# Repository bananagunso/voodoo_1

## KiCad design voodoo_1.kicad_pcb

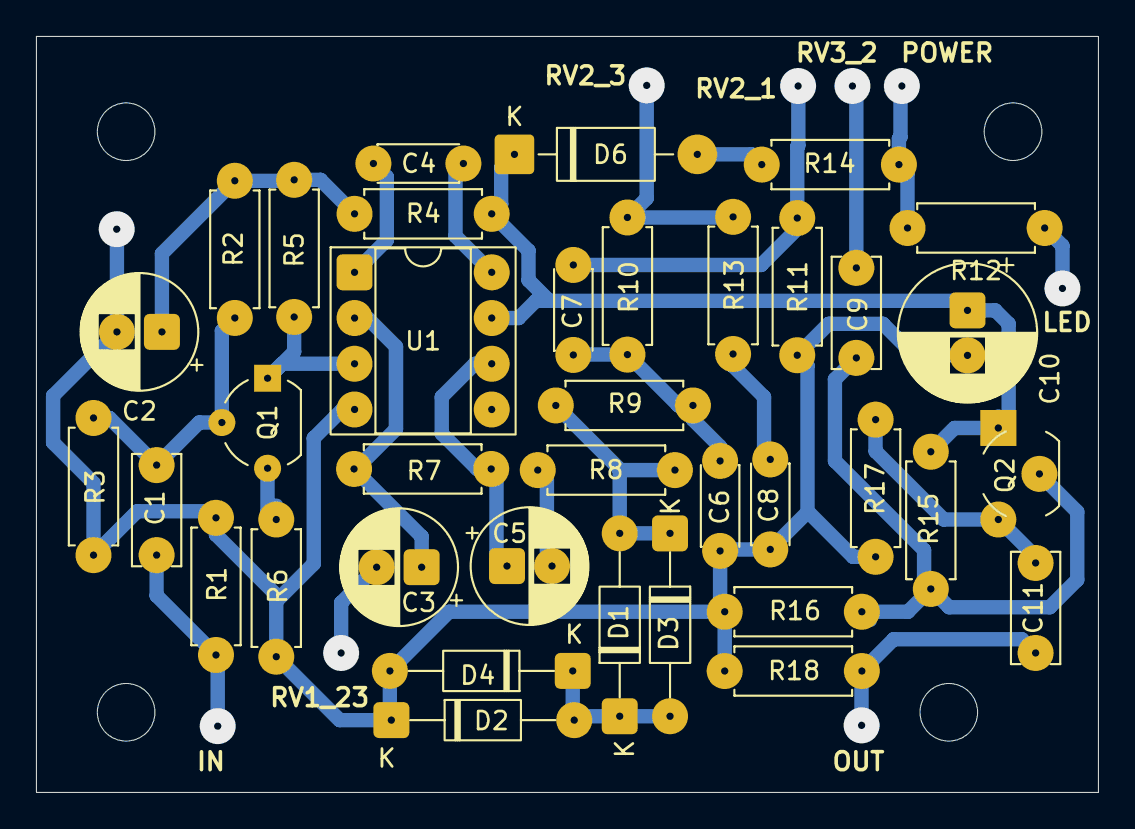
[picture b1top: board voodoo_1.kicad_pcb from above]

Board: 2 copper layers, 59.0 x 42.0 mm, 41 parts (0 on the bottom side), 23 nets.

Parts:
C1, C9, C11: 0.1u; C_Disc_D6.0mm_W2.5mm_P5.00mm
C2: 16v22u; CP_Radial_D6.3mm_P2.50mm
C3, C5: 16v2.2u; CP_Radial_D6.3mm_P2.50mm
C4: 22p; C_Disc_D4.3mm_W1.9mm_P5.00mm
C6: 3300p; C_Disc_D4.3mm_W1.9mm_P5.00mm
C7: 2200p; C_Disc_D4.3mm_W1.9mm_P5.00mm
C8: 470p; C_Disc_D4.3mm_W1.9mm_P5.00mm
C10: 16v220u; CP_Radial_D7.5mm_P2.50mm
D1, D2, D3, D4: 1N4148WT; D_DO-35_SOD27_P10.16mm_Horizontal
D6: 1N4001; D_DO-41_SOD81_P10.16mm_Horizontal
H1, H2, H3, H4: MountingHole; MountingHole_3.2mm_M3
Q1, Q2: 2N2222; TO-92_Wide
R1, R2, R18: 2.2M; R_Axial_DIN0207_L6.3mm_D2.5mm_P7.62mm_Horizontal
R3: 680k; R_Axial_DIN0207_L6.3mm_D2.5mm_P7.62mm_Horizontal
R4, R5: 47k; R_Axial_DIN0207_L6.3mm_D2.5mm_P7.62mm_Horizontal
R6: 22k; R_Axial_DIN0207_L6.3mm_D2.5mm_P7.62mm_Horizontal
R7: 150k; R_Axial_DIN0207_L6.3mm_D2.5mm_P7.62mm_Horizontal
R8, R17: 10k; R_Axial_DIN0207_L6.3mm_D2.5mm_P7.62mm_Horizontal
R9: 1.5k; R_Axial_DIN0207_L6.3mm_D2.5mm_P7.62mm_Horizontal
R10, R11: 39k; R_Axial_DIN0207_L6.3mm_D2.5mm_P7.62mm_Horizontal
R12: 5.6k; R_Axial_DIN0207_L6.3mm_D2.5mm_P7.62mm_Horizontal
R13: 12k; R_Axial_DIN0207_L6.3mm_D2.5mm_P7.62mm_Horizontal
R14: 150; R_Axial_DIN0207_L6.3mm_D2.5mm_P7.62mm_Horizontal
R15: 820k; R_Axial_DIN0207_L6.3mm_D2.5mm_P7.62mm_Horizontal
R16: 1M; R_Axial_DIN0207_L6.3mm_D2.5mm_P7.62mm_Horizontal
U1: LM308; DIP-8_W7.62mm_Socket

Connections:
+9V: R12.2, R14.1
GND: C2.2, C6.2, C8.2, C10.2, D2.1 (K), D4.2 (A), R1.1, R3.1, R6.1, R11.1, R16.1, R17.1, R18.1, U1.4 (V-)
unnamed: C2.1, R2.2, R4.1, R5.2
unnamed: C5.1, R7.2, U1.6
unnamed: C5.2, R8.1
unnamed: C6.1, C7.2, R9.2, R10.1
unnamed: C7.1, R11.2
unnamed: C8.1, R13.1
unnamed: D1.2 (A), D3.1 (K), R8.2, R9.1
unnamed: D1.1 (K), D2.2 (A), D3.2 (A), D4.1 (K)
unnamed: D6.2 (A), R14.2
unnamed: C10.1, D6.1 (K), Q2.1 (C), R4.2, R15.2, U1.7 (V+)
unnamed: C1.1, Q1.2 (B), R2.1, R3.2
unnamed: Q1.1 (C), R5.1, U1.3 (+)
unnamed: Q1.3 (E), R6.2
unnamed: C9.1, Q2.2 (B), R15.1, R16.2
unnamed: C11.2, Q2.3 (E), R17.2
unnamed: R10.2, R13.2
unnamed: C1.2, R1.2
unnamed: C11.1, R18.2
unnamed: C3.1, R7.1, U1.2 (-)
unnamed: C4.1, U1.1 (COMP1)
unnamed: C4.2, U1.8 (COMP2)

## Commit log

2025-10-30 とりあえずICを置く
2025-10-30 回路図作成
2025-10-31 フットプリント割り当て
2025-11-03 部品を配置
2025-11-03 上下幅を修正
2025-11-04 4番ピンがGNDに接続されてなかった
2025-11-10 GNDを1.0mmに、ドリル穴を0.4mmに、部品の配置をやり直し。
2025-11-12 ネジ穴追加、配置修整、線は0.8mm、GNDは1.0mm。
2025-11-12 GNDを0.8に戻してパッドの大きさが小さかったものを2に修正
2025-11-15 2n2222のピンアサイン修正、配置を詰めた。
2025-11-16 C8のコンデンサ470pF -> 4700pF
2025-11-20 配線を修正
2025-11-24 ベタ追加
2025-11-24 ベタを修正
